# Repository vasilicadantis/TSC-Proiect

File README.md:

# OpenBook

Vasilica Danțiș – 332CD

## Diagrama bloc

## BOM

| Componenta                                      | Link                                                                                                                         |
| ------------------------------------------------| -----------------------------------------------------------------------------------------------------------------------------|
| led                                             | [Link](https://www.snapeda.com/parts/KP-1608SURCK/Kingbright/view-part/?company=Politehnica+University+of+Buch&welcome=home&ref=search&t=LED+0603) |
| Button_customv1                                 | [Link](https://industry.panasonic.com/global/en/products/control/switch/light-touch/number/evqpuj02k)                         |
| Eagle_ltspice_c                                 | [Link](https://componentsearchengine.com/part-view/0402WGF3001TCE/UNI-ROYAL(Uniroyal%20Elec))                                 |
| ESP32_WROVER_AVX—SD0805S020S1R0                 | [Link](https://ro.mouser.com/ProductDetail/KYOCERA-AVX/SD0805S020S1R0?qs=jCA%252BPfw4LHbpkAoSnwrdjw%3D%3D)                  |
| ESP32_WROVER_BME680_BME680                      | [Link](https://www.snapeda.com/parts/BME680/Bosch/view-part/?welcome=home)                                                  |
| ESP32_WROVER_EAGLE-LTSPICE_R                    | [Link](https://componentsearchengine.com/part-view/R0402%201%25%20100%20K%20(RC0402FR-07100KL)/YAGEO)                         |
| RCL_CPOL-EU                                     | [Link](https://www.snapeda.com/parts/TAJB475K025RNJ/AVX/view-part/?t=capacitor%203528&con_ref=None)                         |
| SJ                                              | [Link](https://grabcad.com/library/solder-jumpers-1)                                                                          |
| R-URI                                           | [Link](https://componentsearchengine.com/part-view/R0402%201%25%20100%20K%20(RC0402FR-07100KL)/YAGEO)                         |
| ESP32_WROVER_SPARKFUN-DISCRETESEMI_MOSFET_PCH   | [Link](https://componentsearchengine.com/part-view/DMG2305UX-7/Diodes%20Incorporated)                                         |
| ESP32_WROVER_SPARKFUN-IC-POWER_MCP73831         | [Link](https://eu.mouser.com/ProductDetail/Microchip-Technology/MCP73831T-2ACI-OT?qs=yUQqVecv4qvbBQBGbHx0Mw%3D%3D)       |
| TP                                              | Facut Manual (un cilindru)                                                                                                                |
| FH34SRJ-24S-0.5SH_99_                           | [Link](https://componentsearchengine.com/part-view/FH34SRJ-24S-0.5SH(99)/Hirose)                                             |
| MAX17048G+T10                                   | [Link](https://www.snapeda.com/parts/MAX17048G+T10/Analog+Devices/view-part/)                                                |
| SAMACSYS_PARTS_USB4110-GF-A                     | [Link](https://componentsearchengine.com/part-view/USB4110-GF-A/GCT%20(GLOBAL%20CONNECTOR%20TECHNOLOGY))                      |
| QWIIC_CONNECTOR                                 | [Link](https://www.snapeda.com/parts/PRT-14417/SparkFun%20Electronics/view-part/?t=QWIIC_CONNECTORJS-1MM)                     |
| 112A-TAAR-R03_ATTEND                             | [Link](https://componentsearchengine.com/part-view/112A-TAAR-R03%20ATTEND/ATTEND)                                             |
| 744043680IND_4828-WE-TPC_WRE                     | [Link](https://componentsearchengine.com/part-view/744043680/W%C3%BCrth%20Elektronik)                                          |
| BD5229G-TR                                      | [Link](https://componentsearchengine.com/part-view/BD5229G-TR/ROHM%20Semiconductor)                                          |
| CPH3225A                                        | [Link](https://componentsearchengine.com/part-view/CPH3225A/Seiko%20Semiconductors)                                          |
| DS3231SN#                                       | [Link](https://componentsearchengine.com/part-view/DS3231SN%23/Analog%20Devices)                                             |
| ESP32-C6-WROOM-1-N8                             | [Link](https://componentsearchengine.com/part-view/ESP32-C6-WROOM-1-N8/Espressif%20Systems)                                  |
| MBR0530                                         | [Link](https://componentsearchengine.com/part-view/MBR0530/onsemi)                                                           |
| SI1308EDL-T1-GE3                                | [Link](https://componentsearchengine.com/part-view/SI1308EDL-T1-GE3/Vishay)                                                  |
| USBLC6-2SC6Y                                    | [Link](https://componentsearchengine.com/part-view/USBLC6-2SC6Y/STMicroelectronics)                                          |
| W25Q512JVEIQ                                    | [Link](https://componentsearchengine.com/part-view/W25Q512JVEIQ/Winbond)                                                     |
| XC6220A331MR-G                                  | [Link](https://componentsearchengine.com/part-view/XC6220A331MR-G/Torex)                                                     |

## Descriere detaliată a funcționalității hardware

1. **Microcontroller (ESP32-C6)**
   - **Rol:** Asigură controlul central al dispozitivului, conectivitatea Wi-Fi, logica de afișare pe E-Ink și interfața cu utilizatorul (butoane).
   - **Caracteristici:**
     - Integrează un nucleu RISC-V și un subsistem Wi-Fi 6 (802.11ax).
     - Consum redus în modurile de *deep-sleep*, esențial pentru un e-book reader.

2. **E-Ink Display**
   - **Tip:** (ex.) 2.9" EPD (monocrom), cu driver intern sau driver separat.
   - **Interfață cu ESP32-C6:** SPI (poate fi 4-wire SPI cu linii de comandă suplimentare: DC, CS, RST, BUSY).
   - **Motiv:** E-Ink-ul are consum redus de energie, menținând imaginea chiar și fără alimentare (refresh scăzut).

3. **Senzor BME688**
   - **Rol:** Permite ajustarea luminozității (dacă există LED) sau stocarea datelor de mediu.
   - **Interfață:** I2C (implicit) / SPI (opțional).
   - **Consum:** Relativ mic (în jur de câțiva µA în mod de stand-by, dar poate crește la câteva mA în mod de funcționare continuă).

4. **DS3231 RTC**
   - **Rol:** Asigură un ceas de timp real foarte precis, cu consum scăzut.
   - **Interfață:** I2C, cu eventual pin de interrupt (INT/SQW) pentru semnal periodic sau alarmă.
   - **Consum:** Aproximativ 1-2 µA în modul de menținere a ceasului (alimentat direct din baterie).

5. **Memorie externă NOR Flash (W25Q512)**
   - **Rol:** Oferă stocare suplimentară (ex. 64Mbit) pentru fișiere, resurse, cărți electronice etc.
   - **Interfață:** SPI la viteze ridicate (până la 40-80MHz, dacă e specificat).
   - **Consum:** Câțiva mA în scriere/citire și µA în mod standby.

6. **Sistem de alimentare și managementul bateriei**
   - **USB-C Connector:** Permite alimentare la 5V și date (pentru programare/debug).
   - **Battery Charger (MCP73831):** Încarcă Li-Po la 4.2V cu un curent setat prin rezistență PROG (ex. 500mA).
   - **LDO / DC-DC:** Convertește tensiunea bateriei (3.7V nominal) în 3.3V stabil pentru ESP32-C6, E-Ink și restul circuitelor. Dacă se dorește extragerea tensiunii de 5V, se poate folosi un boost converter (DC-DC step-up).
   - **Calcul consum (approx.):**
     - **ESP32-C6:** ~80-240 mA în mod Tx Wi-Fi, <1 mA în modem-sleep, câțiva µA în deep-sleep.
     - **E-Ink:** Consum ridicat doar la refresh (~tens of mA), inactiv aproape 0.
     - **Senzor BME688:** <1 mA tipic (pe I2C) în mod standard, <1 µA în stand-by.
     - **RTC DS3231:** 1-2 µA pentru menținerea ceasului.

7. **Interfața utilizator (Butoane)**
   - 3 butoane SMD (ex. Boot, Change, Reset) conectate la pinii GPIO ai ESP32-C6, cu rezistențe de pull-up/pull-down și debounce minimal (sau software).

8. **Alte considerații**
   - Protecție ESD pe USB, liniile SPI, conectori externi.
   - Test pad-uri: Semnalele principale (MISO, MOSI, RX, GND) expuse pentru programare / debugging.

## Detalii despre pinii ESP32-C6

## Considerații de design PCB

### Rutarea traseelor de alimentare
- Lățime de minimum **0.3 mm** pentru liniile de putere (3V3, 5V, VBAT).
- Lățime de minimum **0.15 mm** pentru liniile de date (SPI, I2C, UART etc.).
- Grosime PCB de maximum **1 mm** pentru a încăpea în carcasă.

### Decuplare
- Condensatoare de **100 nF (0402)** lângă fiecare pin de alimentare al circuitelor integrate (ESP32, BME688, DS3231, Flash).
- Condensatoare mai mari (ex. **4.7 µF ~ 10 µF**) pentru stabilizarea surselor locale.

### Antenă ESP32-C6
- Zona antenei trebuie eliberată de planul de masă și semnale, cu decupaj PCB sub antenă.

### DRC și ERC
- Verificarea regulilor de design: evitarea unghiurilor de 90°; utilizarea via stitching pe planul GND; respectarea reglementărilor de clearance etc.

### Placement
- Componentele SMD sunt plasate exclusiv pe **Top Layer** (conform specificațiilor proiectului).
- Butoanele sunt poziționate ergonomic pentru utilizator.
- Conectorul USB-C este accesibil pe marginea plăcii.

### Via Stitching
- Implementat în jurul ESP32-C6 și al planului de masă pentru reducerea zgomotului EMI.

### Test pad-uri
- Semnalele MISO, MOSI, SCK, GND, 3V3, TX, RX etc. sunt accesibile pentru programare și debugging.

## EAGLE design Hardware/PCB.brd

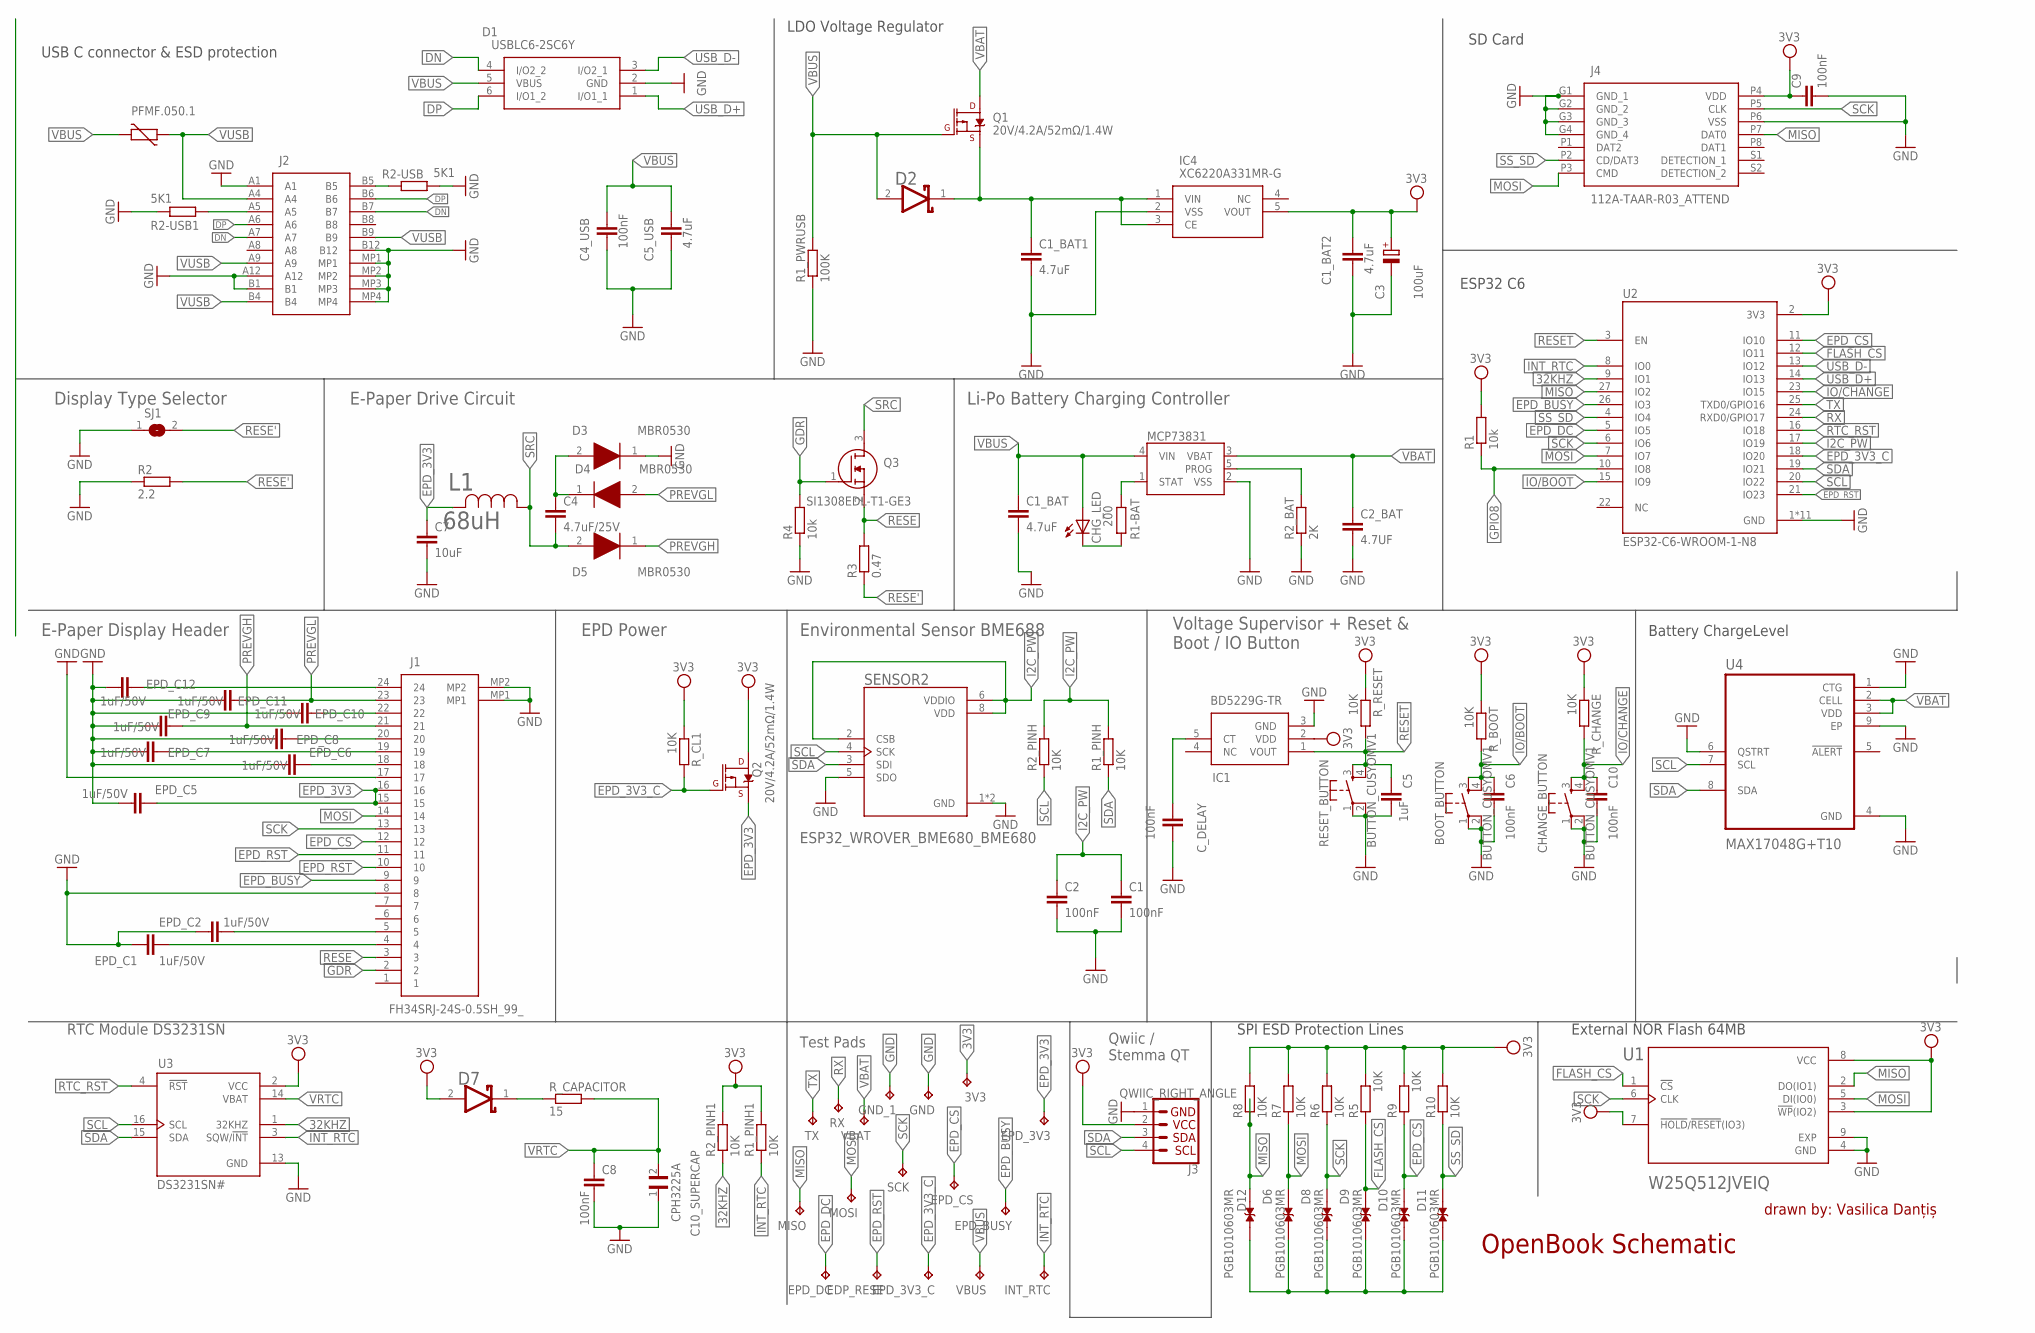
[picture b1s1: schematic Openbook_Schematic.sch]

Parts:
3V3: TPTP20R; TP20R
BOOT_BUTTON: BUTTON_CUSYOMV1; MYBUTTON
C1, C2, C4_USB, C6, C8, C9, C10: 100nF; ESP32_WROVER_EAGLE-LTSPICE_C0402
C1_BAT, C1_BAT1, C1_BAT2, C5_USB: 4.7uF; ESP32_WROVER_EAGLE-LTSPICE_C0402
C2_BAT: 4.7UF; ESP32_WROVER_EAGLE-LTSPICE_C0402
C3: 100uF; RCL_CT3528
C4: 4.7uF/25V; ESP32_WROVER_EAGLE-LTSPICE_C0402
C5: 1uF; ESP32_WROVER_EAGLE-LTSPICE_C0402
C7: 10uF; ESP32_WROVER_EAGLE-LTSPICE_C0402
C10_SUPERCAP: CPH3225A; CAPCP3225X100N
CHANGE_BUTTON: BUTTON_CUSYOMV1; MYBUTTON
CHG_LED: ADAFRUIT_LEDCHIP-LED0603; ADAFRUIT_CHIP-LED0603
C_DELAY: 100nF; ESP32_WROVER_EAGLE-LTSPICE_C0402
D1: USBLC6-2SC6Y; SOT95P280X145-6N
D2, D7: ESP32_WROVER_AVX---SD0805S020S1R0_AVX_SD0805S020S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; ESP32_WROVER_AVX---SD0805S020S1R0_AVX_SD0805S020S1R0_0
D3, D4, D5: MBR0530; SOD3716X135N
D6, D8, D9, D10, D11, D12: PGB1010603MR; DIOC1608X36N
EDP_RESE: TPTP20R; TP20R
EPD_3V3, EPD_3V3_C: TPTP20R; TP20R
EPD_BUSY: TPTP20R; TP20R
EPD_C1, EPD_C2, EPD_C5, EPD_C6, EPD_C7, EPD_C8, EPD_C9, EPD_C10, EPD_C11, EPD_C12: 1uF/50V; ESP32_WROVER_EAGLE-LTSPICE_C0402
EPD_CS: TPTP20R; TP20R
EPD_DC: TPTP20R; TP20R
GND: TPTP20R; TP20R
GND_1: TPTP20R; TP20R
IC1: BD5229G-TR; SOT95P280X120-5N
IC4: XC6220A331MR-G; SOT95P280X120-5N
INT_RTC: TPTP20R; TP20R
J1: FH34SRJ-24S-0.5SH_99_; FH34SRJ24S05SH99
J2: SAMACSYS_PARTS_USB4110-GF-A; SAMACSYS_PARTS_USB4110GFA
J3: QWIIC_RIGHT_ANGLE; JST04_1MM_RA
J4: 112A-TAAR-R03_ATTEND; 112ATAARR03ATTEND
L1: 68uH; IND_4828-WE-TPC_WRE
MCP73831: ESP32_WROVER_SPARKFUN-IC-POWER_MCP73831; ESP32_WROVER_SPARKFUN-IC-POWER_SOT23-5
MISO: TPTP20R; TP20R
MOSI: TPTP20R; TP20R
PFMF.050.1: ESP32C6_VARISTORCN1812; ESP32C6_VARISTOR_CT/CN1812
Q1, Q2: 20V/4.2A/52mΩ/1.4W; ESP32_WROVER_SPARKFUN-DISCRETESEMI_SOT23-3
Q3: SI1308EDL-T1-GE3; SOT65P210X110-3N
R1, R4: 10k; ESP32_WROVER_EAGLE-LTSPICE_R0402
R1-BAT: 200; ESP32_WROVER_EAGLE-LTSPICE_R0402
R1_PINH, R1_PINH1, R2_PINH, R2_PINH1, R5, R6, R7, R8, R9, R10: 10K; ESP32_WROVER_EAGLE-LTSPICE_R0402
R1_PWRUSB: 100K; ESP32_WROVER_EAGLE-LTSPICE_R0402
R2: 2.2; ESP32_WROVER_EAGLE-LTSPICE_R0402
R2-USB, R2-USB1: 5K1; ESP32_WROVER_EAGLE-LTSPICE_R0402
R2_BAT: 2K; ESP32_WROVER_EAGLE-LTSPICE_R0402
R3: 0.47; ESP32_WROVER_EAGLE-LTSPICE_R0402
RESET_BUTTON: BUTTON_CUSYOMV1; MYBUTTON
RX: TPTP20R; TP20R
R_BOOT: 10K; ESP32_WROVER_EAGLE-LTSPICE_R0402
R_CAPACITOR: 15; ESP32_WROVER_EAGLE-LTSPICE_R0402
R_CHANGE: 10K; ESP32_WROVER_EAGLE-LTSPICE_R0402
R_CL1: 10K; ESP32_WROVER_EAGLE-LTSPICE_R0402
R_RESET: 10K; ESP32_WROVER_EAGLE-LTSPICE_R0402
SCK: TPTP20R; TP20R
SENSOR2: ESP32_WROVER_BME680_BME680; ESP32_WROVER_BME680_PSON80P300X300X100-8N
SJ1: SJ
TX: TPTP20R; TP20R
U1: W25Q512JVEIQ; SON127P600X800X80-9N
U2: ESP32-C6-WROOM-1-N8; XCVR_ESP32-C6-WROOM-1-N8
U3: DS3231SN#; SOIC127P1032X265-16N
U4: MAX17048G+T10; SON50P200X200X80-9N
VBAT: TPTP20R; TP20R
VBUS: TPTP20R; TP20R

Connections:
3V3: 3V3.TP, C1_BAT2.1, C3.+, C9.1, D7.2 (ANODE), IC1.2 (VDD), IC4.5 (VOUT), J3.2, J4.P4 (VDD), Q2.3 (D), R1.2, R1_PINH1.2, R2_PINH1.2, R5.2, R6.2, R7.2, R8.2, R9.2, R10.2, R_BOOT.1, R_CHANGE.1, R_CL1.1, R_RESET.1, U1.3 (!WP!(IO2)), U1.7 (!HOLD!/!RESET!(IO3)), U1.8 (VCC), U2.2 (3V3), U3.2 (VCC)
32KHZ: R2_PINH1.1, U2.9 (IO1), U3.1 (32KHZ)
DN: D1.4 (I/O2_2), J2.A7, J2.B7
DP: D1.6 (I/O1_2), J2.A6, J2.B6
EPD_3V3: C7.1, EPD_3V3.TP, EPD_C5.1, J1.15, J1.16, L1.2, Q2.2 (S)
EPD_3V3_C: EPD_3V3_C.TP, Q2.1 (G), R_CL1.2, U2.18 (IO20)
EPD_BUSY: EPD_BUSY.TP, J1.9, U2.26 (IO3)
EPD_CS: D10.1, EPD_CS.TP, J1.12, R9.1, U2.11 (IO10)
EPD_DC: EPD_DC.TP, U2.5 (IO5)
EPD_RST: EDP_RESE.TP, J1.10, J1.11, U2.21 (IO23)
FLASH_CS: D9.1, R5.1, U1.1 (!CS), U2.12 (IO11)
GDR: J1.2, Q3.1 (G), R4.2
GND: BOOT_BUTTON.1, BOOT_BUTTON.2, C1.2, C1_BAT.2, C1_BAT1.2, C1_BAT2.2, C2.2, C2_BAT.2, C3.-, C4_USB.2, C5.2, C5_USB.2, C6.2, C7.2, C8.2, C9.2, C10.2, C10_SUPERCAP.1, CHANGE_BUTTON.1, CHANGE_BUTTON.2, C_DELAY.2, D1.2 (GND), D3.1 (K), EPD_C1.2, EPD_C2.2, EPD_C5.2, EPD_C6.2, EPD_C7.2, EPD_C8.2, EPD_C9.2, EPD_C10.2, EPD_C11.2, EPD_C12.2, GND.TP, GND_1.TP, IC1.3 (GND), IC4.2 (VSS), J1.8, J1.17, J1.MP1, J1.MP2, J2.A1, J2.A12, J2.B1, J2.B12, J2.MP1, J2.MP2, J2.MP3, J2.MP4, J3.1, J4.G1 (GND_1), J4.G2 (GND_2), J4.G3 (GND_3), J4.G4 (GND_4), J4.P6 (VSS), MCP73831.2 (VSS), R1_PWRUSB.1, R2.1, R2-USB.2, R2-USB1.1, R2_BAT.1, R4.1, RESET_BUTTON.1, RESET_BUTTON.2, SENSOR2.1 (GND), SENSOR2.5 (SDO), SENSOR2.7 (GND), SJ1.1, U1.4 (GND), U1.9 (EXP), U2.1 (GND), U2.28 (GND), U2.29_1 (GND), U2.29_2 (GND), U2.29_3 (GND), U2.29_4 (GND), U2.29_5 (GND), U2.29_6 (GND), U2.29_7 (GND), U2.29_8 (GND), U2.29_9 (GND), U3.13 (GND), U4.1 (CTG), U4.4 (GND), U4.6 (QSTRT), U4.9 (EP); also elsewhere on the board
GPIO8: R1.1, U2.10 (IO8)
I2C_PW: C1.1, C2.1, R1_PINH.2, R2_PINH.2, SENSOR2.2 (CSB), SENSOR2.6 (VDDIO), SENSOR2.8 (VDD), U2.17 (IO19)
INT_RTC: INT_RTC.TP, R1_PINH1.1, U2.8 (IO0), U3.3 (SQW/!INT)
IO/BOOT: BOOT_BUTTON.3, BOOT_BUTTON.4, C6.1, R_BOOT.2, U2.15 (IO9)
IO/CHANGE: C10.1, CHANGE_BUTTON.3, CHANGE_BUTTON.4, R_CHANGE.2, U2.23 (IO15)
MISO: D12.1, J4.P7 (DAT0), MISO.TP, R8.1, U1.2 (DO(IO1)), U2.27 (IO2)
MOSI: D6.1, J1.14, J4.P3 (CMD), MOSI.TP, R7.1, U1.5 (DI(IO0)), U2.7 (IO7)
unnamed: C1_BAT1.1, D2.1 (CATHODE), IC4.1 (VIN), IC4.3 (CE), Q1.2 (S)
unnamed: C4.1, D3.2 (A), D4.1 (K)
unnamed: J2.B5, R2-USB.1
unnamed: J2.A5, R2-USB1.2
unnamed: CHG_LED.C, R1-BAT.1
unnamed: MCP73831.1 (STAT), R1-BAT.2
unnamed: EPD_C12.1, J1.24
unnamed: MCP73831.5 (PROG), R2_BAT.2
unnamed: C_DELAY.1, IC1.5 (CT)
unnamed: D7.1 (CATHODE), R_CAPACITOR.1
unnamed: EPD_C10.1, J1.22
unnamed: EPD_C8.1, J1.20
unnamed: EPD_C7.1, J1.19
unnamed: EPD_C6.1, J1.18
unnamed: EPD_C2.1, J1.5
unnamed: EPD_C1.1, J1.4
unnamed: D6.2, D8.2, D9.2, D10.2, D11.2, D12.2
RESE: J1.3, Q3.2 (S), R3.2
RESE': R2.2, R3.1, SJ1.2
RESET: C5.1, IC1.1 (VOUT), RESET_BUTTON.3, RESET_BUTTON.4, R_RESET.2, U2.3 (EN)
RTC_RST: U2.16 (IO18), U3.4 (!RST)
RX: RX.TP, U2.24 (RXD0/GPIO17)
SCK: D8.1, J1.13, J4.P5 (CLK), R6.1, SCK.TP, U1.6 (CLK), U2.6 (IO6)
SCL: J3.4, R2_PINH.1, SENSOR2.4 (SCK), U2.20 (IO22), U3.16 (SCL), U4.7 (SCL)
SDA: J3.3, R1_PINH.1, SENSOR2.3 (SDI), U2.19 (IO21), U3.15 (SDA), U4.8 (SDA)
SRC: C4.2, D5.2 (A), L1.1, Q3.3 (D)
SS_SD: D11.1, J4.P2 (CD/DAT3), R10.1, U2.4 (IO4)
TX: TX.TP, U2.25 (TXD0/GPIO16)
USB_D+: D1.1 (I/O1_1), U2.14 (IO13)
USB_D-: D1.3 (I/O2_1), U2.13 (IO12)
VBAT: C2_BAT.1, MCP73831.3 (VBAT), Q1.3 (D), U4.2 (CELL), U4.3 (VDD), VBAT.TP
VBUS: C1_BAT.1, C4_USB.1, C5_USB.1, CHG_LED.A, D1.5 (VBUS), D2.2 (ANODE), MCP73831.4 (VIN), PFMF.050.1.2, Q1.1 (G), R1_PWRUSB.2, VBUS.TP
VRTC: C8.1, C10_SUPERCAP.2, R_CAPACITOR.2, U3.14 (VBAT)
VUSB: J2.A4, J2.A9, J2.B4, J2.B9, PFMF.050.1.1

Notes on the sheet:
USB C connector & ESD protection
LDO Voltage Regulator
SD Card
ESP32 C6
Battery ChargeLevel
External NOR Flash 64MB
SPI ESD Protection Lines
Qwiic / Stemma QT
Test Pads
RTC Module DS3231SN
Voltage Supervisor + Reset & Boot / IO Button
Environmental Sensor BME688
EPD Power
E-Paper Display Header
Li-Po Battery Charging Controller
E-Paper Drive Circuit
Display Type Selector
OpenBook Schematic
drawn by: Vasilica Danțiș

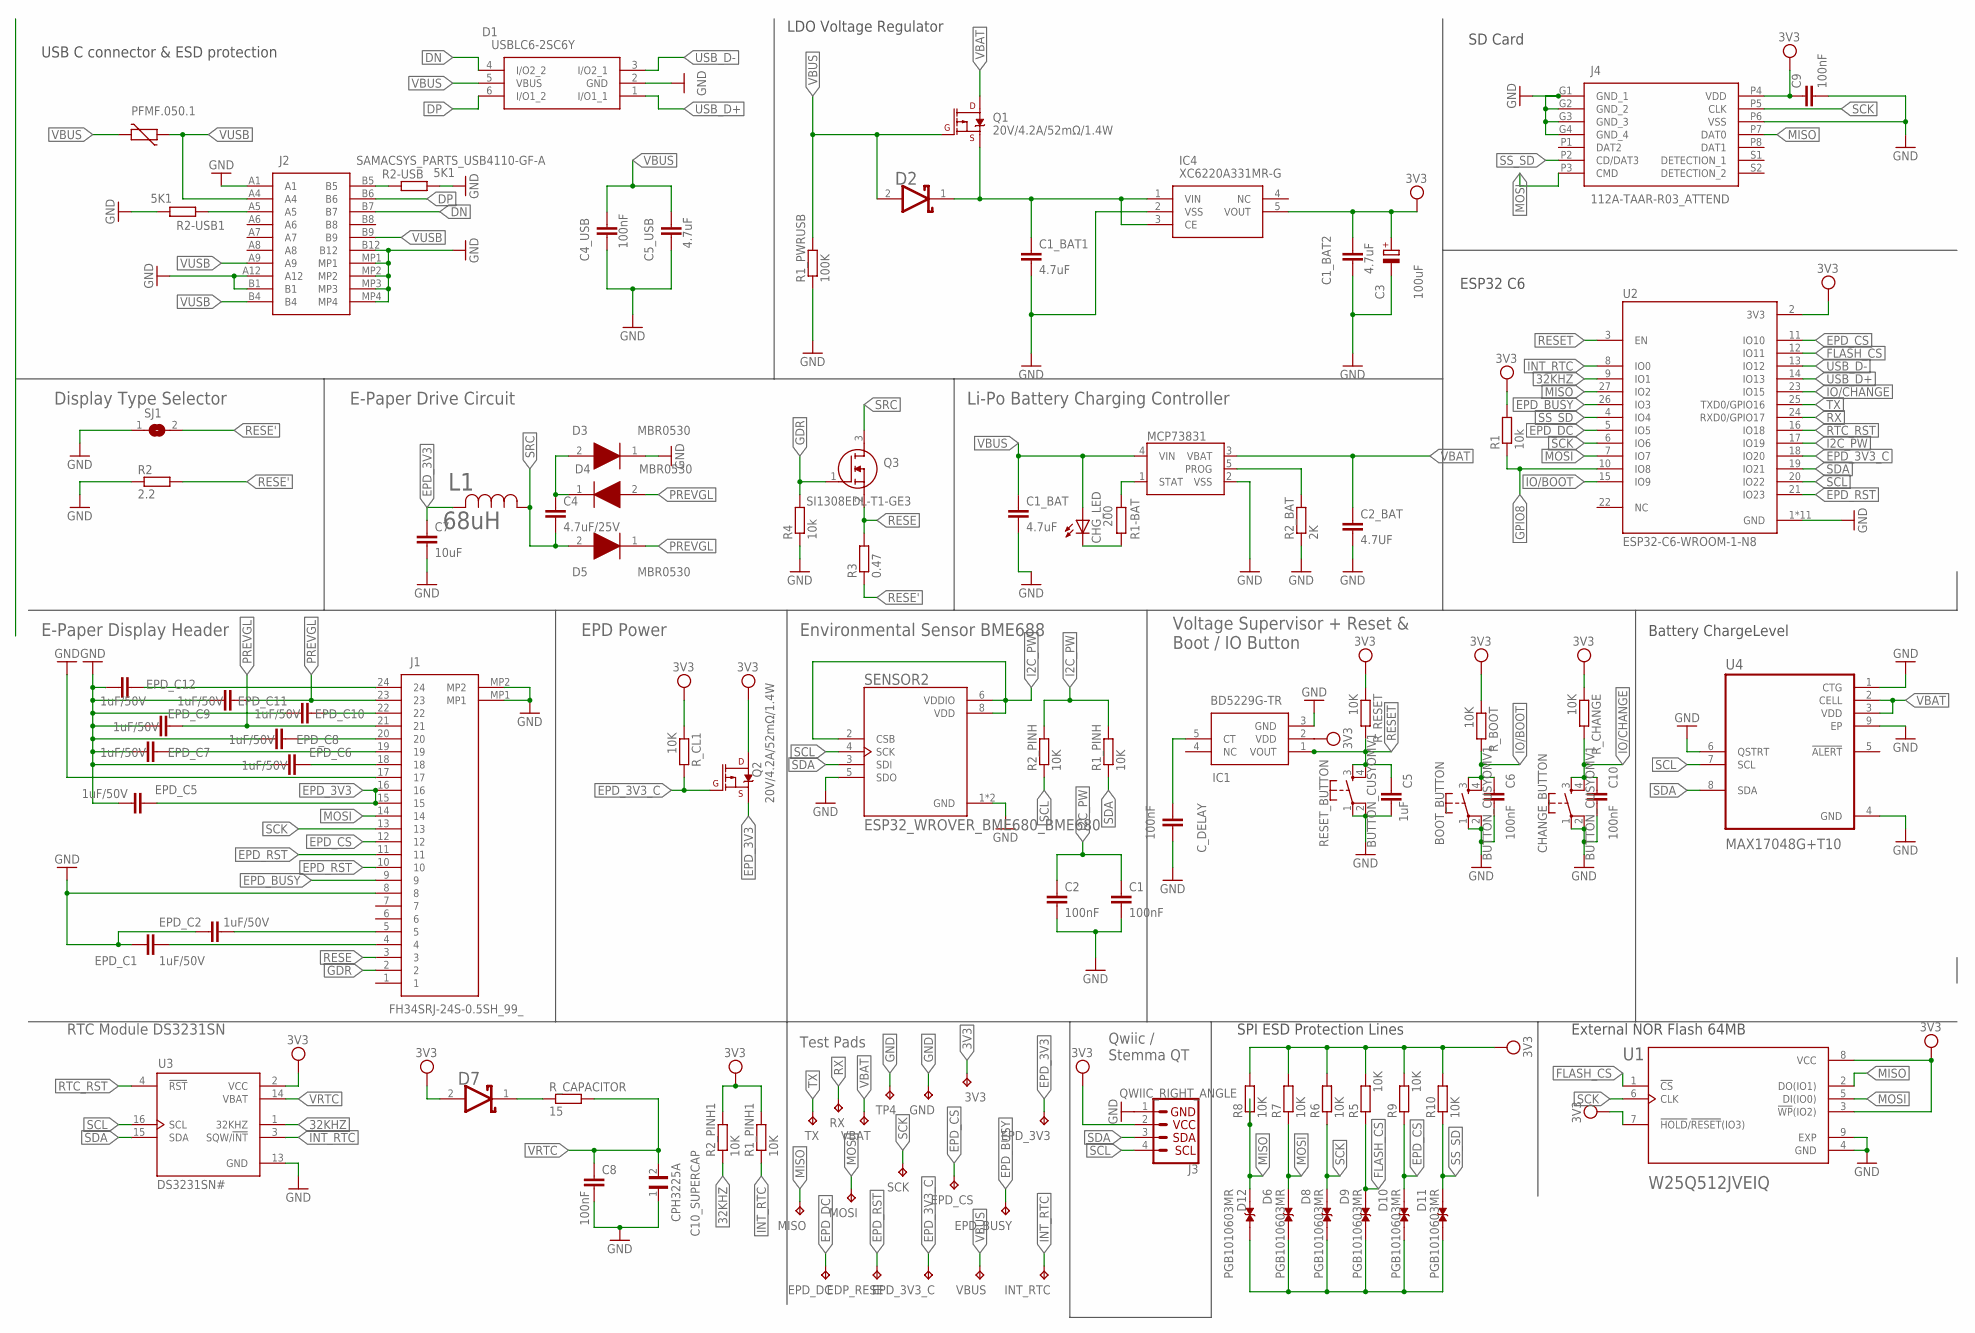
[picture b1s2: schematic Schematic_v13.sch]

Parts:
3V3: TPTP20R; TP20R
BOOT_BUTTON: BUTTON_CUSYOMV1; MYBUTTON
C1, C2, C4_USB, C6, C8, C9, C10: 100nF; ESP32_WROVER_EAGLE-LTSPICE_C0402
C1_BAT, C1_BAT1, C1_BAT2, C5_USB: 4.7uF; ESP32_WROVER_EAGLE-LTSPICE_C0402
C2_BAT: 4.7UF; ESP32_WROVER_EAGLE-LTSPICE_C0402
C3: 100uF; RCL_CT3528
C4: 4.7uF/25V; ESP32_WROVER_EAGLE-LTSPICE_C0402
C5: 1uF; ESP32_WROVER_EAGLE-LTSPICE_C0402
C7: 10uF; ESP32_WROVER_EAGLE-LTSPICE_C0402
C10_SUPERCAP: CPH3225A; CAPCP3225X100N
CHANGE_BUTTON: BUTTON_CUSYOMV1; MYBUTTON
CHG_LED: ADAFRUIT_LEDCHIP-LED0603; ADAFRUIT_CHIP-LED0603
C_DELAY: 100nF; ESP32_WROVER_EAGLE-LTSPICE_C0402
D1: USBLC6-2SC6Y; SOT95P280X145-6N
D2, D7: ESP32_WROVER_AVX---SD0805S020S1R0_AVX_SD0805S020S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; ESP32_WROVER_AVX---SD0805S020S1R0_AVX_SD0805S020S1R0_0
D3, D4, D5: MBR0530; SOD3716X135N
D6, D8, D9, D10, D11, D12: PGB1010603MR; DIOC1608X36N
EDP_RESE: TPTP20R; TP20R
EPD_3V3, EPD_3V3_C: TPTP20R; TP20R
EPD_BUSY: TPTP20R; TP20R
EPD_C1, EPD_C2, EPD_C5, EPD_C6, EPD_C7, EPD_C8, EPD_C9, EPD_C10, EPD_C11, EPD_C12: 1uF/50V; ESP32_WROVER_EAGLE-LTSPICE_C0402
EPD_CS: TPTP20R; TP20R
EPD_DC: TPTP20R; TP20R
GND: TPTP20R; TP20R
IC1: BD5229G-TR; SOT95P280X120-5N
IC4: XC6220A331MR-G; SOT95P280X120-5N
INT_RTC: TPTP20R; TP20R
J1: FH34SRJ-24S-0.5SH_99_; FH34SRJ24S05SH99
J2: SAMACSYS_PARTS_USB4110-GF-A; SAMACSYS_PARTS_USB4110GFA
J3: QWIIC_RIGHT_ANGLE; JST04_1MM_RA
J4: 112A-TAAR-R03_ATTEND; 112ATAARR03ATTEND
L1: 68uH; IND_4828-WE-TPC_WRE
MCP73831: ESP32_WROVER_SPARKFUN-IC-POWER_MCP73831; ESP32_WROVER_SPARKFUN-IC-POWER_SOT23-5
MISO: TPTP20R; TP20R
MOSI: TPTP20R; TP20R
PFMF.050.1: ESP32C6_VARISTORCN1812; ESP32C6_VARISTOR_CT/CN1812
Q1, Q2: 20V/4.2A/52mΩ/1.4W; ESP32_WROVER_SPARKFUN-DISCRETESEMI_SOT23-3
Q3: SI1308EDL-T1-GE3; SOT65P210X110-3N
R1, R4: 10k; ESP32_WROVER_EAGLE-LTSPICE_R0402
R1-BAT: 200; ESP32_WROVER_EAGLE-LTSPICE_R0402
R1_PINH, R1_PINH1, R2_PINH, R2_PINH1, R5, R6, R7, R8, R9, R10: 10K; ESP32_WROVER_EAGLE-LTSPICE_R0402
R1_PWRUSB: 100K; ESP32_WROVER_EAGLE-LTSPICE_R0402
R2: 2.2; ESP32_WROVER_EAGLE-LTSPICE_R0402
R2-USB, R2-USB1: 5K1; ESP32_WROVER_EAGLE-LTSPICE_R0402
R2_BAT: 2K; ESP32_WROVER_EAGLE-LTSPICE_R0402
R3: 0.47; ESP32_WROVER_EAGLE-LTSPICE_R0402
RESET_BUTTON: BUTTON_CUSYOMV1; MYBUTTON
RX: TPTP20R; TP20R
R_BOOT: 10K; ESP32_WROVER_EAGLE-LTSPICE_R0402
R_CAPACITOR: 15; ESP32_WROVER_EAGLE-LTSPICE_R0402
R_CHANGE: 10K; ESP32_WROVER_EAGLE-LTSPICE_R0402
R_CL1: 10K; ESP32_WROVER_EAGLE-LTSPICE_R0402
R_RESET: 10K; ESP32_WROVER_EAGLE-LTSPICE_R0402
SCK: TPTP20R; TP20R
SENSOR2: ESP32_WROVER_BME680_BME680; ESP32_WROVER_BME680_PSON80P300X300X100-8N
SJ1: SJ
TP4: TPTP20R; TP20R
TX: TPTP20R; TP20R
U1: W25Q512JVEIQ; SON127P600X800X80-9N
U2: ESP32-C6-WROOM-1-N8; XCVR_ESP32-C6-WROOM-1-N8
U3: DS3231SN#; SOIC127P1032X265-16N
U4: MAX17048G+T10; SON50P200X200X80-9N
VBAT: TPTP20R; TP20R
VBUS: TPTP20R; TP20R

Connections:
3V3: 3V3.TP, C1_BAT2.1, C3.+, C9.1, D7.2 (ANODE), IC1.2 (VDD), IC4.5 (VOUT), J3.2, J4.P4 (VDD), Q2.3 (D), R1.2, R1_PINH1.2, R2_PINH1.2, R5.2, R6.2, R7.2, R8.2, R9.2, R10.2, R_BOOT.1, R_CHANGE.1, R_CL1.1, R_RESET.1, U1.3 (!WP!(IO2)), U1.7 (!HOLD!/!RESET!(IO3)), U1.8 (VCC), U2.2 (3V3), U3.2 (VCC)
32KHZ: R2_PINH1.1, U2.9 (IO1), U3.1 (32KHZ)
DN: D1.4 (I/O2_2), J2.B7; also elsewhere on the board
DP: D1.6 (I/O1_2), J2.B6; also elsewhere on the board
EPD_3V3: C7.1, EPD_3V3.TP, EPD_C5.1, J1.15, J1.16, L1.2, Q2.2 (S)
EPD_3V3_C: EPD_3V3_C.TP, Q2.1 (G), R_CL1.2, U2.18 (IO20)
EPD_BUSY: EPD_BUSY.TP, J1.9, U2.26 (IO3)
EPD_CS: D10.1, EPD_CS.TP, J1.12, R9.1, U2.11 (IO10)
EPD_DC: EPD_DC.TP, U2.5 (IO5)
EPD_RST: EDP_RESE.TP, J1.10, J1.11, U2.21 (IO23)
FLASH_CS: D9.1, R5.1, U1.1 (!CS), U2.12 (IO11)
GDR: J1.2, Q3.1 (G), R4.2
GND: BOOT_BUTTON.1, BOOT_BUTTON.2, C1.2, C1_BAT.2, C1_BAT1.2, C1_BAT2.2, C2.2, C2_BAT.2, C3.-, C4_USB.2, C5.2, C5_USB.2, C6.2, C7.2, C8.2, C9.2, C10.2, C10_SUPERCAP.1, CHANGE_BUTTON.1, CHANGE_BUTTON.2, C_DELAY.2, D1.2 (GND), D3.1 (K), EPD_C1.2, EPD_C2.2, EPD_C5.2, EPD_C6.2, EPD_C7.2, EPD_C8.2, EPD_C9.2, EPD_C10.2, EPD_C11.2, EPD_C12.2, GND.TP, IC1.3 (GND), IC4.2 (VSS), J1.8, J1.17, J1.MP1, J1.MP2, J2.A1, J2.A12, J2.B1, J2.B12, J2.MP1, J2.MP2, J2.MP3, J2.MP4, J3.1, J4.G1 (GND_1), J4.G2 (GND_2), J4.G3 (GND_3), J4.G4 (GND_4), J4.P6 (VSS), MCP73831.2 (VSS), R1_PWRUSB.1, R2.1, R2-USB.2, R2-USB1.1, R2_BAT.1, R4.1, RESET_BUTTON.1, RESET_BUTTON.2, SENSOR2.1 (GND), SENSOR2.5 (SDO), SENSOR2.7 (GND), SJ1.1, TP4.TP, U1.4 (GND), U1.9 (EXP), U2.1 (GND), U2.28 (GND), U2.29_1 (GND), U2.29_2 (GND), U2.29_3 (GND), U2.29_4 (GND), U2.29_5 (GND), U2.29_6 (GND), U2.29_7 (GND), U2.29_8 (GND), U2.29_9 (GND), U3.13 (GND), U4.1 (CTG), U4.4 (GND), U4.6 (QSTRT), U4.9 (EP); also elsewhere on the board
GPIO8: R1.1, U2.10 (IO8)
I2C_PW: C1.1, C2.1, R1_PINH.2, R2_PINH.2, SENSOR2.2 (CSB), SENSOR2.6 (VDDIO), SENSOR2.8 (VDD), U2.17 (IO19)
INT_RTC: INT_RTC.TP, R1_PINH1.1, U2.8 (IO0), U3.3 (SQW/!INT)
IO/BOOT: BOOT_BUTTON.3, BOOT_BUTTON.4, C6.1, R_BOOT.2, U2.15 (IO9)
IO/CHANGE: C10.1, CHANGE_BUTTON.3, CHANGE_BUTTON.4, R_CHANGE.2, U2.23 (IO15)
MISO: D12.1, J4.P7 (DAT0), MISO.TP, R8.1, U1.2 (DO(IO1)), U2.27 (IO2)
MOSI: D6.1, J1.14, J4.P3 (CMD), MOSI.TP, R7.1, U1.5 (DI(IO0)), U2.7 (IO7)
unnamed: C1_BAT1.1, D2.1 (CATHODE), IC4.1 (VIN), IC4.3 (CE), Q1.2 (S)
unnamed: C4.1, D3.2 (A), D4.1 (K)
unnamed: J2.B5, R2-USB.1
unnamed: J2.A5, R2-USB1.2
unnamed: CHG_LED.C, R1-BAT.1
unnamed: MCP73831.1 (STAT), R1-BAT.2
unnamed: EPD_C12.1, J1.24
unnamed: MCP73831.5 (PROG), R2_BAT.2
unnamed: C_DELAY.1, IC1.5 (CT)
unnamed: D7.1 (CATHODE), R_CAPACITOR.1
unnamed: EPD_C10.1, J1.22
unnamed: EPD_C8.1, J1.20
unnamed: EPD_C7.1, J1.19
unnamed: EPD_C6.1, J1.18
unnamed: EPD_C2.1, J1.5
unnamed: EPD_C1.1, J1.4
unnamed: D6.2, D8.2, D9.2, D10.2, D11.2, D12.2
RESE: J1.3, Q3.2 (S), R3.2
RESE': R2.2, R3.1, SJ1.2
RESET: C5.1, IC1.1 (VOUT), RESET_BUTTON.3, RESET_BUTTON.4, R_RESET.2, U2.3 (EN)
RTC_RST: U2.16 (IO18), U3.4 (!RST)
RX: RX.TP, U2.24 (RXD0/GPIO17)
SCK: D8.1, J1.13, J4.P5 (CLK), R6.1, SCK.TP, U1.6 (CLK), U2.6 (IO6)
SCL: J3.4, R2_PINH.1, SENSOR2.4 (SCK), U2.20 (IO22), U3.16 (SCL), U4.7 (SCL)
SDA: J3.3, R1_PINH.1, SENSOR2.3 (SDI), U2.19 (IO21), U3.15 (SDA), U4.8 (SDA)
SRC: C4.2, D5.2 (A), L1.1, Q3.3 (D)
SS_SD: D11.1, J4.P2 (CD/DAT3), R10.1, U2.4 (IO4)
TX: TX.TP, U2.25 (TXD0/GPIO16)
USB_D+: D1.1 (I/O1_1), U2.14 (IO13)
USB_D-: D1.3 (I/O2_1), U2.13 (IO12)
VBAT: C2_BAT.1, MCP73831.3 (VBAT), Q1.3 (D), U4.2 (CELL), U4.3 (VDD), VBAT.TP
VBUS: C1_BAT.1, C4_USB.1, C5_USB.1, CHG_LED.A, D1.5 (VBUS), D2.2 (ANODE), MCP73831.4 (VIN), PFMF.050.1.2, Q1.1 (G), R1_PWRUSB.2, VBUS.TP
VRTC: C8.1, C10_SUPERCAP.2, R_CAPACITOR.2, U3.14 (VBAT)
VUSB: J2.A4, J2.A9, J2.B4, J2.B9, PFMF.050.1.1

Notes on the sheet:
USB C connector & ESD protection
LDO Voltage Regulator
SD Card
ESP32 C6
Battery ChargeLevel
External NOR Flash 64MB
SPI ESD Protection Lines
Qwiic / Stemma QT
Test Pads
RTC Module DS3231SN
Voltage Supervisor + Reset & Boot / IO Button
Environmental Sensor BME688
EPD Power
E-Paper Display Header
Li-Po Battery Charging Controller
E-Paper Drive Circuit
Display Type Selector

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
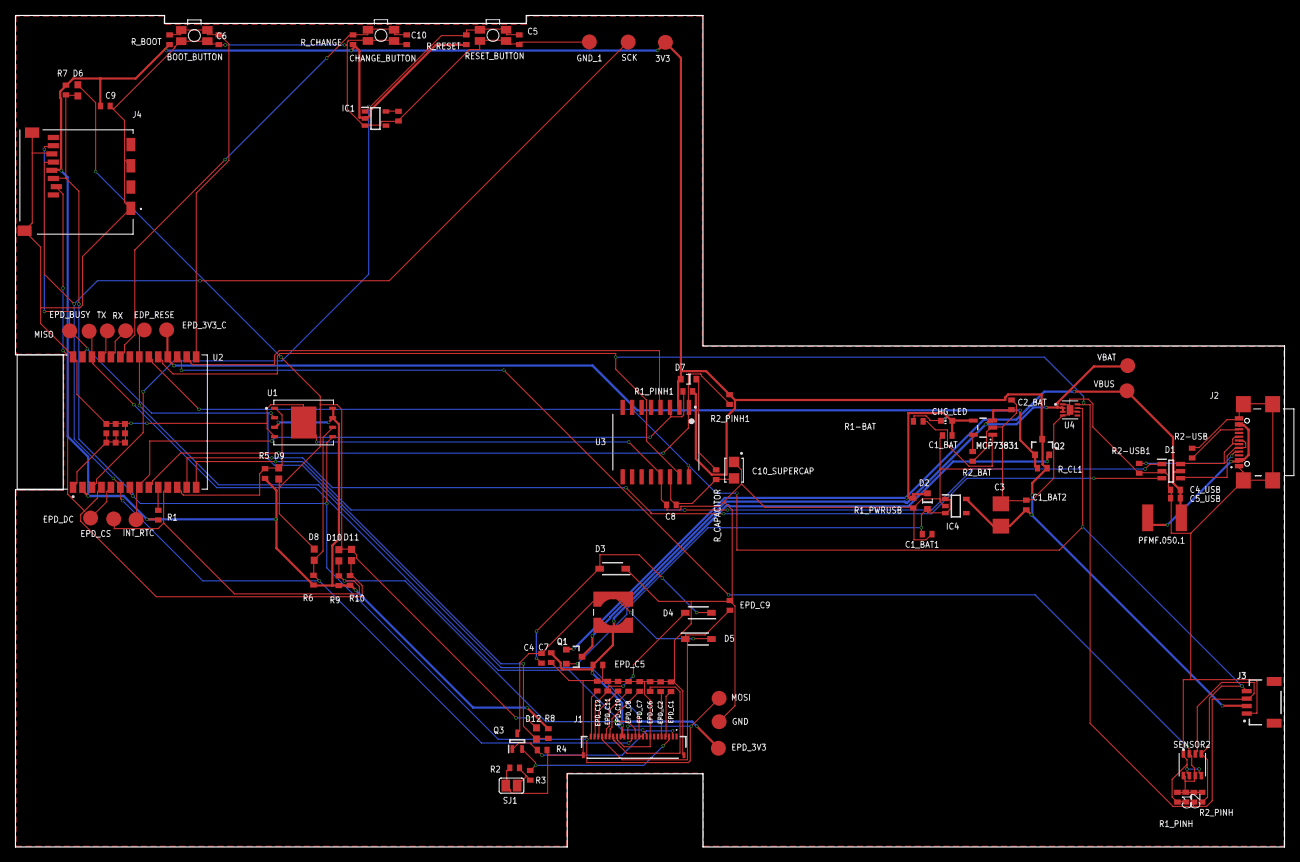
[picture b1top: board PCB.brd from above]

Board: 2 copper layers, 170.2 x 111.5 mm, 103 parts (0 on the bottom side), 56 nets.

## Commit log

2025-04-14 Solved issues

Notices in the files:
parts and their libraries:
DeskAssistant v19 v1: COPYRIGHT: Copyright (C) 2024 Ultra Librarian. All rights reserved.
